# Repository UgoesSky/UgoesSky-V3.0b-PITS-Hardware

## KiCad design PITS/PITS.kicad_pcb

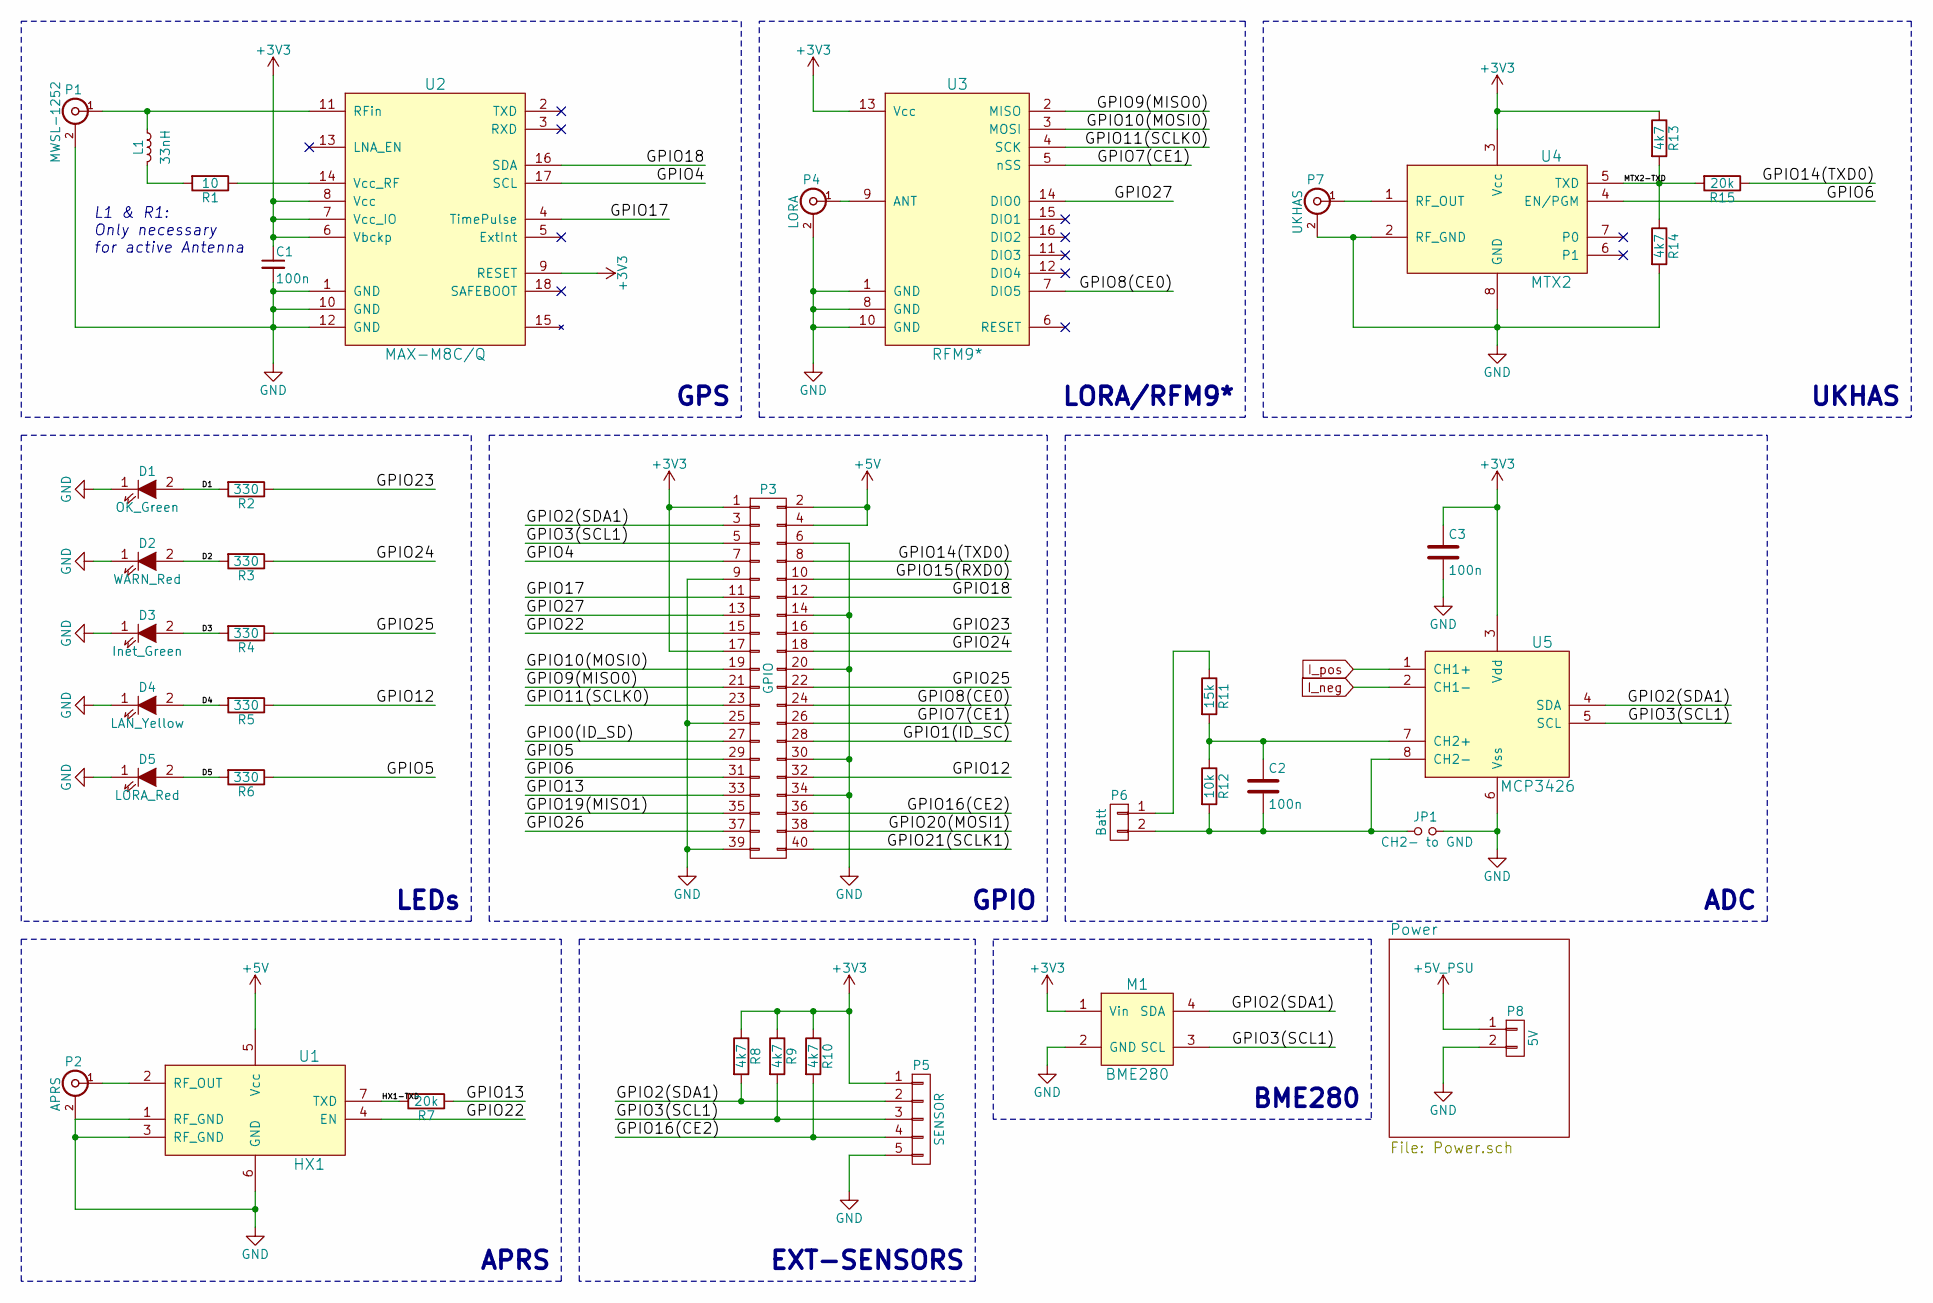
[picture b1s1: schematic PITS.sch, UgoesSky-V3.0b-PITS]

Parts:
C1, C2, C3: 100n; C_0603_HandSoldering
D1: OK_Green; LED_0603
D2: WARN_Red; LED_0603
D3: Inet_Green; LED_0603
D4: LAN_Yellow; LED_0603
D5: LORA_Red; LED_0603
JP1: CH2- to GND; R_0603_HandSoldering
L1: 33nH; R_0805_HandSoldering
M1: BME280
P1: MWSL-1252; MWSL1252
P2: APRS; SMA_Edge_small
P3: GPIO; Socket_Strip_Straight_2x20
P4: LORA; SMA_Edge_small
P5: SENSOR; SMD_5_xsmall
P6: Batt; SMD_2_xsmall
P7: UKHAS; SMA_Edge_small
P8: 5V; SMD_2_xsmall
R1: 10; R_0603_HandSoldering
R2, R3, R4, R5, R6: 330; R_0603_HandSoldering
R7, R15: 20k; R_0603_HandSoldering
R8, R9, R10, R13, R14: 4k7; R_0603_HandSoldering
R11: 15k; R_0805_HandSoldering
R12: 10k; R_0805_HandSoldering
U1: HX1; HX1_Horizontal
U2: MAX-M8C/Q; MAX-M8
U3: RFM9*; RFM9xW
U4: MTX2
U5: MCP3426; SOIC-8_3.9x4.9mm_Pitch1.27mm

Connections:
+3V3: C1.1, C3.1, M1.1 (Vin), P3.1, P3.17, P5.1, R8.1, R9.1, R10.1, R13.1, U2.6 (Vbckp), U2.7 (Vcc_IO), U2.8 (Vcc), U2.9 (RESET), U3.13 (Vcc), U4.3 (Vcc), U5.3 (Vdd)
/D1: D1.2 (A), R2.2
/D2: D2.2 (A), R3.2
/D3: D3.2 (A), R4.2
/D4: D4.2 (A), R5.2
/D5: D5.2 (A), R6.2
/GPIO0(ID_SD): P3.27
/GPIO1(ID_SC): P3.28
/GPIO2(SDA1): M1.4 (SDA), P3.3, P5.2, R8.2, U5.4 (SDA)
/GPIO3(SCL1): M1.3 (SCL), P3.5, P5.3, R9.2, U5.5 (SCL)
/GPIO4: P3.7, U2.17 (SCL)
/GPIO5: P3.29, R6.1
/GPIO6: P3.31, U4.4 (EN/PGM)
/GPIO7(CE1): P3.26, U3.5 (nSS)
/GPIO8(CE0): P3.24, U3.7 (DIO5)
/GPIO9(MISO0): P3.21, U3.2 (MISO)
/GPIO10(MOSI0): P3.19, U3.3 (MOSI)
/GPIO11(SCLK0): P3.23, U3.4 (SCK)
/GPIO12: P3.32, R5.1
/GPIO13: P3.33, R7.1
/GPIO14(TXD0): P3.8, R15.1
/GPIO15(RXD0): P3.10
/GPIO16(CE2): P3.36, P5.4, R10.2
/GPIO17: P3.11, U2.4 (TimePulse)
/GPIO18: P3.12, U2.16 (SDA)
/GPIO19(MISO1): P3.35
/GPIO20(MOSI1): P3.38
/GPIO21(SCLK1): P3.40
/GPIO22: P3.15, U1.4 (EN)
/GPIO23: P3.16, R2.1
/GPIO24: P3.18, R3.1
/GPIO25: P3.22, R4.1
/GPIO26: P3.37
/GPIO27: P3.13, U3.14 (DIO0)
/HX1-TXD: R7.2, U1.7 (TXD)
/MTX2-TXD: R13.2, R14.1, R15.2, U4.5 (TXD)
GND: C1.2, C3.2, D1.1 (K), D2.1 (K), D3.1 (K), D4.1 (K), D5.1 (K), JP1.2, M1.2 (GND), P1.2 (Ext), P2.2 (Ext), P3.6, P3.9, P3.14, P3.20, P3.25, P3.30, P3.34, P3.39, P4.2 (Ext), P5.5, P7.2 (Ext), P8.2, R14.2, U1.1 (RF_GND), U1.3 (RF_GND), U1.6 (GND), U2.1 (GND), U2.10 (GND), U2.12 (GND), U3.1 (GND), U3.8 (GND), U3.10 (GND), U4.2 (RF_GND), U4.8 (GND), U5.6 (Vss); also elsewhere on the board
I_neg: P3.2, P3.4, U1.5 (Vcc), U5.2 (CH1-); also elsewhere on the board
I_pos: P8.1, U5.1 (CH1+); also elsewhere on the board
unnamed: C2.1, R11.2, R12.1, U5.7 (CH2+)
unnamed: C2.2, JP1.1, P6.2, R12.2, U5.8 (CH2-)
unnamed: L1.1, P1.1 (In), U2.11 (RFin)
unnamed: L1.2, R1.2
unnamed: P2.1 (In), U1.2 (RF_OUT)
unnamed: P4.1 (In), U3.9 (ANT)
unnamed: P6.1, R11.1
unnamed: P7.1 (In), U4.1 (RF_OUT)
unnamed: R1.1, U2.14 (Vcc_RF)

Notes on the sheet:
LEDs
ADC
GPIO
LORA/RFM9*
UKHAS
APRS
GPS
EXT-SENSORS
BME280
L1 & R1: Only necessary for active Antenna

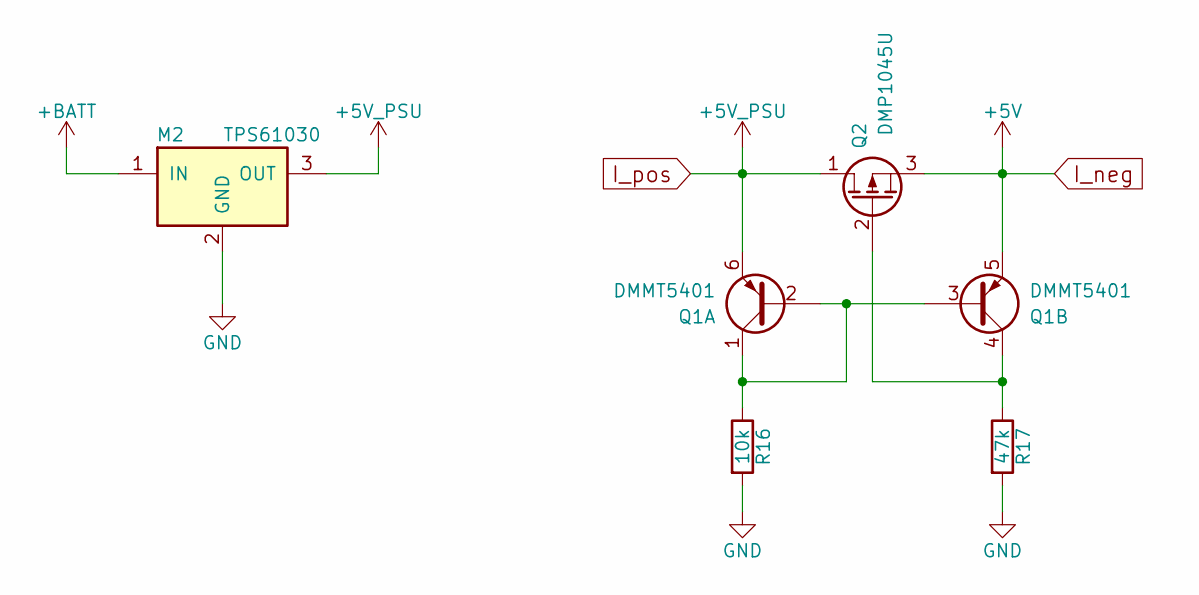
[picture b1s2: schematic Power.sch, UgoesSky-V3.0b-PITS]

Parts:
M2: TPS61030
Q1: DMMT5401; SOT-23-6_Handsoldering
Q2: DMP1045U; SOT-23_Handsoldering
R16: 10k; R_0603_HandSoldering
R17: 47k; R_0603_HandSoldering

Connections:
GND: M2.2 (GND), R16.2, R17.2; also elsewhere on the board
I_neg: Q1.5 (E), Q2.3 (S); also elsewhere on the board
I_pos: M2.3 (OUT), Q1.6 (E), Q2.1 (D); also elsewhere on the board
unnamed: Q1.1 (C), Q1.2 (B), Q1.3 (B), R16.1
unnamed: Q1.4 (C), Q2.2 (G), R17.1

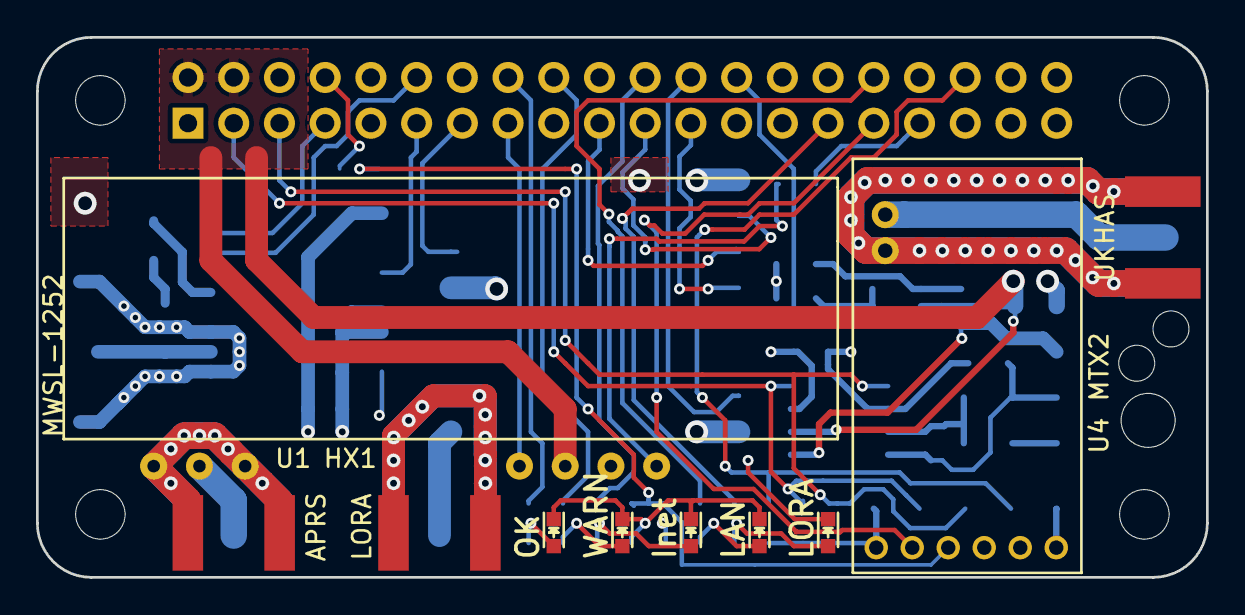
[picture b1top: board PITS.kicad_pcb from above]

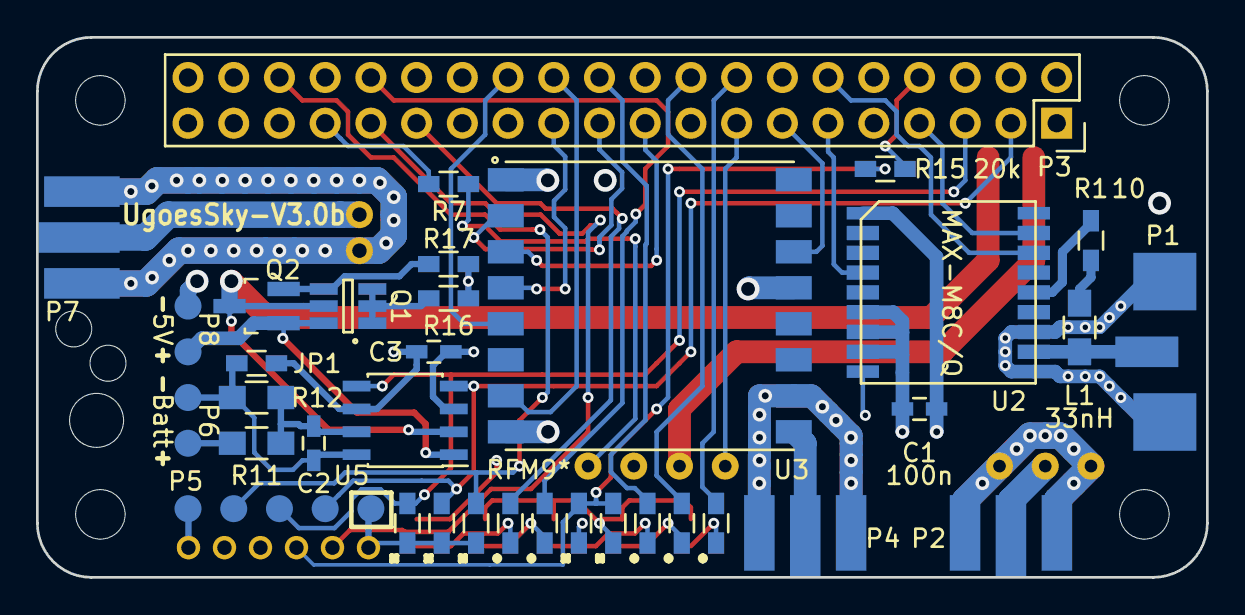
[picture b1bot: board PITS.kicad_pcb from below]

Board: 4 copper layers, 65.0 x 30.0 mm, 42 parts (35 on the bottom side), 43 nets.

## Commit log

2016-11-01 original files and pictures
2016-11-01 added dataaheets
2016-11-01 schematic
2016-11-03 board - not finished
2017-01-04 first finished layout
2017-08-09 old layout - commit for backup
2017-08-09 some files
2017-08-09 working on layout
2017-08-11 SMA 3D
2017-08-11 layout - work in progress
2017-08-11 added pictures and datasheets
2017-08-11 Layout TPS61030
2017-08-12 3D HX1
2017-08-12 3D TPS61030
2017-08-12 layout for zero - work in progress - backup before pin header change
2017-08-12 layout - work in progress - first placement
2017-08-13 layout - work in progress - power net
2017-08-14 layout - work in progress - first digital nets
2017-08-15 3D MWSL1252
2017-08-15 Datasheet MWSL1252
2017-08-15 layout - work in progress - backup GPS antenne change
2017-08-15 3D MWSL1252 add colours
2017-08-16 layout - work in progress - RFM, LEDs, UBLOX
2017-08-20 neue Pinbelegung
2017-08-21 Layout - MTX2, HX1 and LEDs
2017-08-21 ADC, BME280 and power switch
2017-10-28 Layout almost finished
2017-10-28 3D BME280
2017-10-28 Checkt and updated
2017-10-28 custom page layout
2017-10-28 Cleand up plan
2017-11-16 Fix #5
2017-11-16 Fix #6
2017-11-16 Fix #7
2017-11-16 Fix #8 & #9
2017-11-16 Fix #11
2017-11-16 Fix #12
2017-11-16 Added GND Jumper on CH2- of ADC
2017-11-16 updated Annotation
2017-11-16 export schematic
2018-01-16 Some cleanup
2018-01-16 update 3D model
2018-01-21 BME280 3D model
2018-01-22 PCB save
2018-01-29 PCB save befor rerouting power lines
2018-01-29 removed scound LORA led
2018-03-21 add BME280 datasheet
2018-04-14 all power routing done
2018-04-29 all routing finished!
2018-05-08 new Annotation and netlist
2018-05-08 fertiggit add Pinbelegung.ods !
2018-05-09 fertig
2018-05-09 filled zones
2018-08-21 some changes to save
2018-08-21 Datasheets
